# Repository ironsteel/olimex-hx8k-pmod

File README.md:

# Olimex PMOD Expansion for iCE40HX8K-EVB

_NOT READY YET_

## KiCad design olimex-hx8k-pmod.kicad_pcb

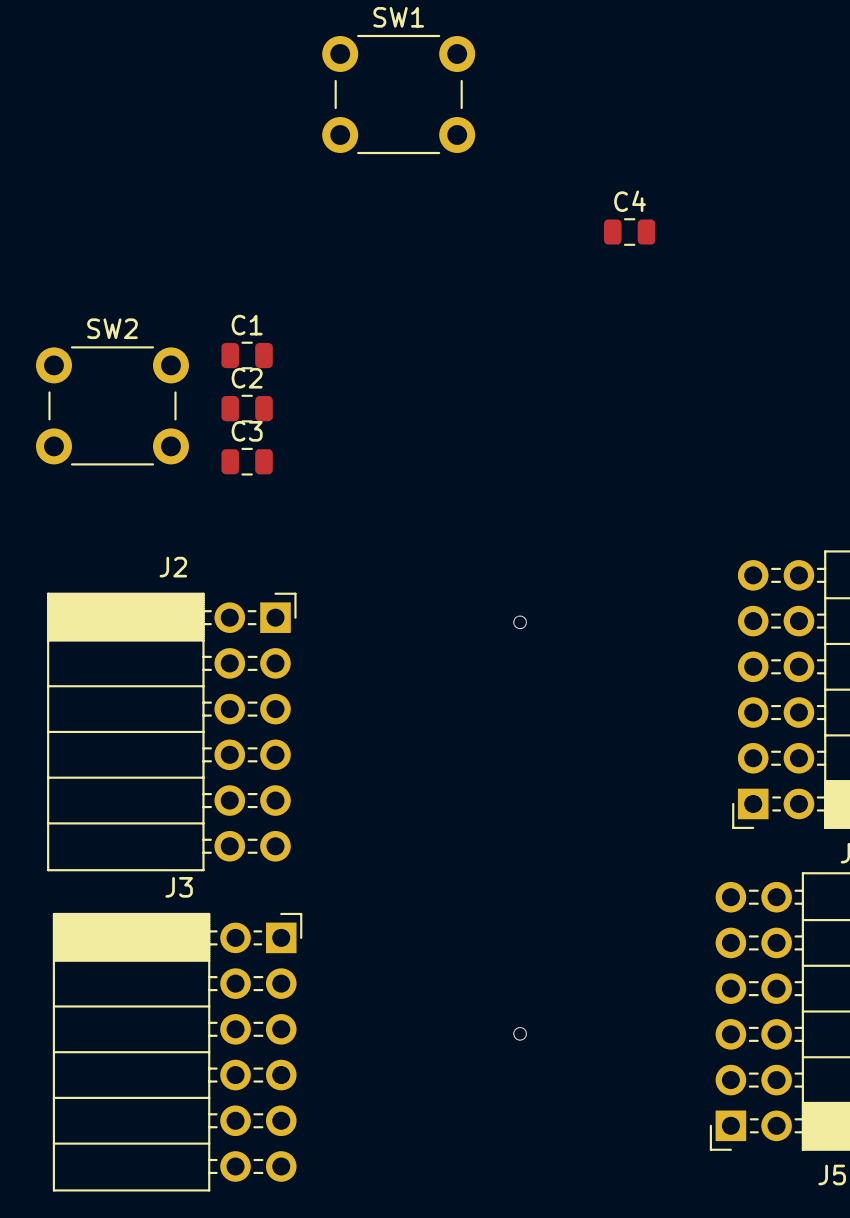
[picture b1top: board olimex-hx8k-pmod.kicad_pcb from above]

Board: 2 copper layers, 11 parts (1 on the bottom side), 36 nets, no tracks yet.

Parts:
C1, C2, C3, C4: 10n; C_0805_2012Metric
J1: Conn_02x20_Odd_Even_FPGA; GPCB127SMT-02X20(YA-V36P-2X20-LF)
J2, J3, J4, J5: PMOD; PinSocket_2x06_P2.54mm_Horizontal
SW1, SW2: SW_SPST; SW_PUSH_6mm

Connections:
+3V3: C1.1, C2.1, C3.1, C4.1, J1.3, J1.5, J2.6, J2.12, J3.6, J3.12, J4.6, J4.12, J5.6, J5.12
/PMOD0_1: J1.7, J2.4
/PMOD0_2: J1.9, J2.10
/PMOD0_3: J1.11, J2.3
/PMOD0_4: J1.13, J2.9
/PMOD0_5: J1.15, J2.2
/PMOD0_6: J1.17, J2.8
/PMOD0_7: J1.19, J2.1
/PMOD0_8: J1.21, J2.7
/PMOD1_1: J1.23, J3.4
/PMOD1_2: J1.25, J3.10
/PMOD1_3: J1.27, J3.3
/PMOD1_4: J1.29, J3.9
/PMOD1_5: J1.31, J3.2
/PMOD1_6: J1.33, J3.8
/PMOD1_7: J1.35, J3.1
/PMOD1_8: J1.37, J3.7
/PMOD2_1: J1.8, J4.1
/PMOD2_2: J1.10, J4.7
/PMOD2_3: J1.12, J4.2
/PMOD2_4: J1.14, J4.8
/PMOD2_5: J1.16, J4.3
/PMOD2_6: J1.18, J4.9
/PMOD2_7: J1.20, J4.4
/PMOD2_8: J1.22, J4.10
/PMOD3_1: J1.24, J5.1
/PMOD3_2: J1.26, J5.7
/PMOD3_3: J1.28, J5.2
/PMOD3_4: J1.30, J5.8
/PMOD3_5: J1.32, J5.3
/PMOD3_6: J1.34, J5.9
/PMOD3_7: J1.36, J5.4
/PMOD3_8: J1.38, J5.10
GND: C1.2, C2.2, C3.2, C4.2, J1.2, J1.4, J2.5, J2.11, J3.5, J3.11, J4.5, J4.11, J5.5, J5.11, SW1.1, SW2.2
unnamed: J1.39, SW1.2
unnamed: J1.40, SW2.1

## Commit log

2019-08-03 Add schematics
2019-11-11 Move schematic symbols to project library
2019-11-17 Rearrange pmod connections for easier routing
    Add custom footprints for pmod connector and olimex expansion connector
